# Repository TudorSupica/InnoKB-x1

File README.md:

# InnoKB-x1
 A DIY mechanical keyboard based on the ATMega32U4 MCU

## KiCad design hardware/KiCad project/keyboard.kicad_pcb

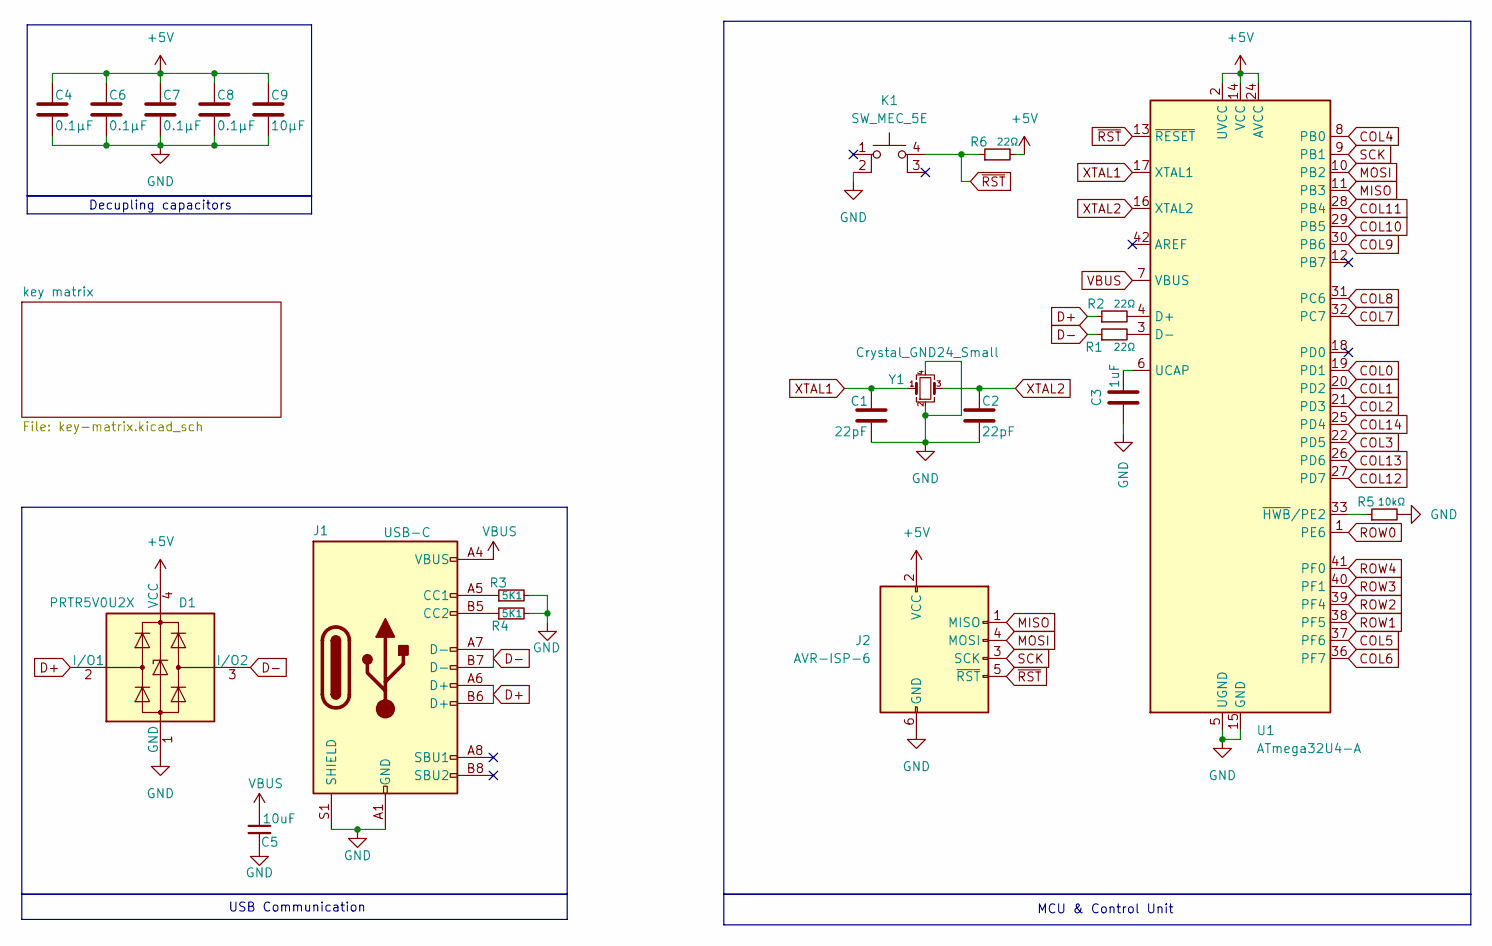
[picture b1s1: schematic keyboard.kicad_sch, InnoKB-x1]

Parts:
C1, C2: 22pF; C_0805_2012Metric_Pad1.18x1.45mm_HandSolder
C3: 1uF; C_0805_2012Metric_Pad1.18x1.45mm_HandSolder
C4, C6, C7, C8: 0.1μF; C_0805_2012Metric_Pad1.18x1.45mm_HandSolder
C5: 10uF; C_0805_2012Metric_Pad1.18x1.45mm_HandSolder
C9: 10μF; C_0805_2012Metric_Pad1.18x1.45mm_HandSolder
D1: PRTR5V0U2X; SOT-143
J1: USB-C; GSB1C41110SSHR
J2: AVR-ISP-6; PinHeader_1x06_P1.27mm_Vertical
K1: SW_MEC_5E; SW_PUSH_6mm
R1, R2, R6: 22Ω; C_0805_2012Metric_Pad1.18x1.45mm_HandSolder
R3, R4: 5K1; C_0805_2012Metric_Pad1.18x1.45mm_HandSolder
R5: 10kΩ; C_0805_2012Metric_Pad1.18x1.45mm_HandSolder
U1: ATmega32U4-A; TQFP-44_10x10mm_P0.8mm
Y1: Crystal_GND24_Small; Crystal_HC49-U-3Pin_Vertical

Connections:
+5V: C4.1, C6.1, C7.1, C8.1, C9.1, D1.4 (VCC), J2.2 (VCC), R6.2, U1.2 (UVCC), U1.14 (VCC), U1.24 (AVCC), U1.34 (VCC), U1.44 (AVCC)
COL0: U1.19 (PD1); also elsewhere on the board
COL1: U1.20 (PD2); also elsewhere on the board
COL2: U1.21 (PD3); also elsewhere on the board
COL3: U1.22 (PD5); also elsewhere on the board
COL4: U1.8 (PB0); also elsewhere on the board
COL5: U1.37 (PF6); also elsewhere on the board
COL6: U1.36 (PF7); also elsewhere on the board
COL7: U1.32 (PC7); also elsewhere on the board
COL8: U1.31 (PC6); also elsewhere on the board
COL9: U1.30 (PB6); also elsewhere on the board
COL10: U1.29 (PB5); also elsewhere on the board
COL11: U1.28 (PB4); also elsewhere on the board
COL12: U1.27 (PD7); also elsewhere on the board
COL13: U1.26 (PD6); also elsewhere on the board
COL14: U1.25 (PD4); also elsewhere on the board
D+: D1.2 (I/O1), J1.A6 (D+), J1.B6 (D+), R2.1
D-: D1.3 (I/O2), J1.A7 (D-), J1.B7 (D-), R1.1
GND: C1.2, C2.2, C3.1, C4.2, C5.2, C6.2, C7.2, C8.2, C9.2, D1.1 (GND), J1.A1 (GND), J1.A12 (GND), J1.B1 (GND), J1.B12 (GND), J1.S1 (SHIELD), J2.6 (GND), K1.2, R3.2, R4.2, R5.2, U1.5 (UGND), U1.15 (GND), U1.23 (GND), U1.35 (GND), U1.43 (GND), Y1.2, Y1.4
MISO: J2.1 (MISO), U1.11 (PB3)
MOSI: J2.4 (MOSI), U1.10 (PB2)
unnamed: J1.A5 (CC1), R3.1
unnamed: J1.B5 (CC2), R4.1
unnamed: R2.2, U1.4 (D+)
unnamed: R1.2, U1.3 (D-)
unnamed: C3.2, U1.6 (UCAP)
unnamed: R5.1, U1.33 (~HWB/PE2)
ROW0: U1.1 (PE6); also elsewhere on the board
ROW1: U1.38 (PF5); also elsewhere on the board
ROW2: U1.39 (PF4); also elsewhere on the board
ROW3: U1.40 (PF1); also elsewhere on the board
ROW4: U1.41 (PF0); also elsewhere on the board
SCK: J2.3 (SCK), U1.9 (PB1)
VBUS: C5.1, J1.A4 (VBUS), J1.A9 (VBUS), J1.B4 (VBUS), J1.B9 (VBUS), U1.7 (VBUS)
XTAL1: C1.1, U1.17 (XTAL1), Y1.1
XTAL2: C2.1, U1.16 (XTAL2), Y1.3
~RST: J2.5 (~RST), K1.4 (A), R6.1, U1.13 (~RESET)

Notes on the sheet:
USB Communication
Decupling capacitors
MCU & Control Unit

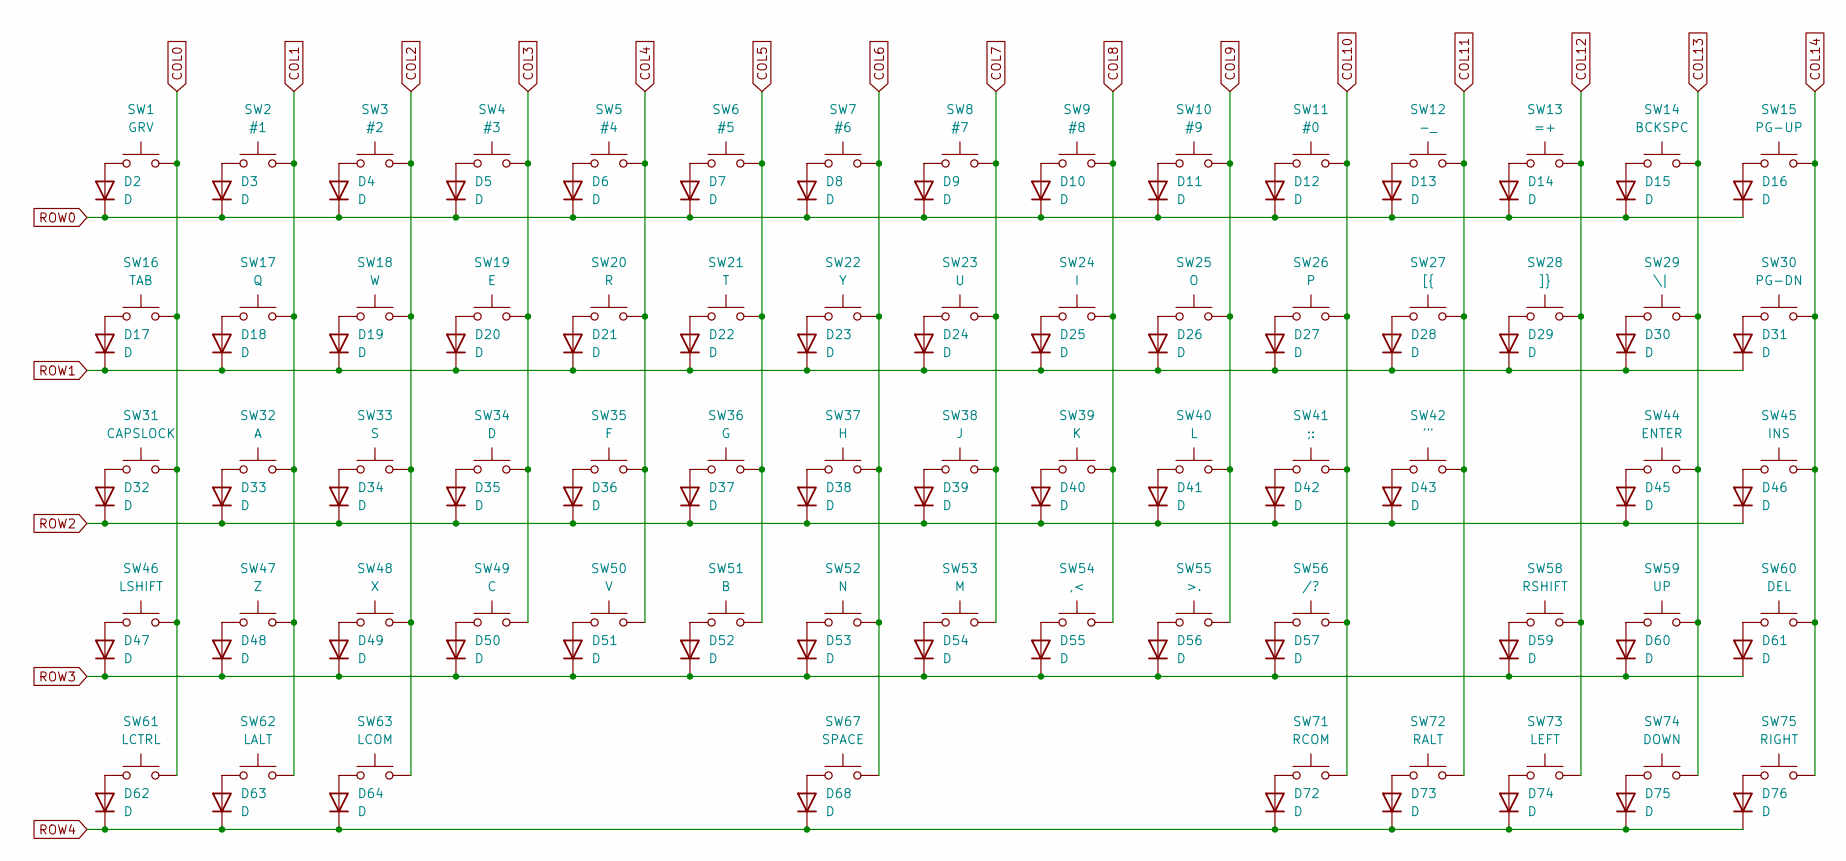
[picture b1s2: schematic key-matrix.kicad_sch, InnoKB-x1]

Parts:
D2, D3, D4, D5, D6, D7, D8, D9, D10, D11, D12, D13, D14, D15, D16, D17, D18, D19, D20, D21, D22, D23, D24, D25, D26, D27, D28, D29, D30, D31, D32, D33, D34, D35, D36, D37, D38, D39, D40, D41, D42, D43, D45, D46, D47, D48, D49, D50, D51, D52, D53, D54, D55, D56, D57, D59, D60, D61, D62, D63, D64, D68, D72, D73, D74, D75, D76: D; D_SOD-123
SW1: GRV; SW_Cherry_MX_1.00u_PCB
SW2: #1; SW_Cherry_MX_1.00u_PCB
SW3: #2; SW_Cherry_MX_1.00u_PCB
SW4: #3; SW_Cherry_MX_1.00u_PCB
SW5: #4; SW_Cherry_MX_1.00u_PCB
SW6: #5; SW_Cherry_MX_1.00u_PCB
SW7: #6; SW_Cherry_MX_1.00u_PCB
SW8: #7; SW_Cherry_MX_1.00u_PCB
SW9: #8; SW_Cherry_MX_1.00u_PCB
SW10: #9; SW_Cherry_MX_1.00u_PCB
SW11: #0; SW_Cherry_MX_1.00u_PCB
SW12: -_; SW_Cherry_MX_1.00u_PCB
SW13: =+; SW_Cherry_MX_1.00u_PCB
SW14: BCKSPC; SW_Cherry_MX_2.00u_PCB
SW15: PG-UP; SW_Cherry_MX_1.00u_PCB
SW16: TAB; SW_Cherry_MX_1.50u_PCB
SW17: Q; SW_Cherry_MX_1.00u_PCB
SW18: W; SW_Cherry_MX_1.00u_PCB
SW19: E; SW_Cherry_MX_1.00u_PCB
SW20: R; SW_Cherry_MX_1.00u_PCB
SW21: T; SW_Cherry_MX_1.00u_PCB
SW22: Y; SW_Cherry_MX_1.00u_PCB
SW23: U; SW_Cherry_MX_1.00u_PCB
SW24: I; SW_Cherry_MX_1.00u_PCB
SW25: O; SW_Cherry_MX_1.00u_PCB
SW26: P; SW_Cherry_MX_1.00u_PCB
SW27: [{; SW_Cherry_MX_1.00u_PCB
SW28: ]}; SW_Cherry_MX_1.00u_PCB
SW29: \|; SW_Cherry_MX_1.50u_PCB
SW30: PG-DN; SW_Cherry_MX_1.00u_PCB
SW31: CAPSLOCK; SW_Cherry_MX_1.75u_PCB
SW32: A; SW_Cherry_MX_1.00u_PCB
SW33: S; SW_Cherry_MX_1.00u_PCB
SW34: D; SW_Cherry_MX_1.00u_PCB
SW35: F; SW_Cherry_MX_1.00u_PCB
SW36: G; SW_Cherry_MX_1.00u_PCB
SW37: H; SW_Cherry_MX_1.00u_PCB
SW38: J; SW_Cherry_MX_1.00u_PCB
SW39: K; SW_Cherry_MX_1.00u_PCB
SW40: L; SW_Cherry_MX_1.00u_PCB
SW41: ;:; SW_Cherry_MX_1.00u_PCB
SW42: '"; SW_Cherry_MX_1.00u_PCB
SW44: ENTER; SW_Cherry_MX_2.25u_PCB
SW45: INS; SW_Cherry_MX_1.00u_PCB
SW46: LSHIFT; SW_Cherry_MX_2.25u_PCB
SW47: Z; SW_Cherry_MX_1.00u_PCB
SW48: X; SW_Cherry_MX_1.00u_PCB
SW49: C; SW_Cherry_MX_1.00u_PCB
SW50: V; SW_Cherry_MX_1.00u_PCB
SW51: B; SW_Cherry_MX_1.00u_PCB
SW52: N; SW_Cherry_MX_1.00u_PCB
SW53: M; SW_Cherry_MX_1.00u_PCB
SW54: ,<; SW_Cherry_MX_1.00u_PCB
SW55: >.; SW_Cherry_MX_1.00u_PCB
SW56: /?; SW_Cherry_MX_1.00u_PCB
SW58: RSHIFT; SW_Cherry_MX_1.75u_PCB
SW59: UP; SW_Cherry_MX_1.00u_PCB
SW60: DEL; SW_Cherry_MX_1.00u_PCB
SW61: LCTRL; SW_Cherry_MX_1.50u_PCB
SW62: LALT; SW_Cherry_MX_1.25u_PCB
SW63: LCOM; SW_Cherry_MX_1.50u_PCB
SW67: SPACE; SW_Cherry_MX_6.25u_PCB
SW71: RCOM; SW_Cherry_MX_1.00u_PCB
SW72: RALT; SW_Cherry_MX_1.25u_PCB
SW73: LEFT; SW_Cherry_MX_1.00u_PCB
SW74: DOWN; SW_Cherry_MX_1.00u_PCB
SW75: RIGHT; SW_Cherry_MX_1.00u_PCB

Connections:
COL0: SW1.2, SW16.2, SW31.2, SW46.2, SW61.2; also elsewhere on the board
COL1: SW2.2, SW17.2, SW32.2, SW47.2, SW62.2; also elsewhere on the board
COL2: SW3.2, SW18.2, SW33.2, SW48.2, SW63.2; also elsewhere on the board
COL3: SW4.2, SW19.2, SW34.2, SW49.2; also elsewhere on the board
COL4: SW5.2, SW20.2, SW35.2, SW50.2; also elsewhere on the board
COL5: SW6.2, SW21.2, SW36.2, SW51.2; also elsewhere on the board
COL6: SW7.2, SW22.2, SW37.2, SW52.2, SW67.2; also elsewhere on the board
COL7: SW8.2, SW23.2, SW38.2, SW53.2; also elsewhere on the board
COL8: SW9.2, SW24.2, SW39.2, SW54.2; also elsewhere on the board
COL9: SW10.2, SW25.2, SW40.2, SW55.2; also elsewhere on the board
COL10: SW11.2, SW26.2, SW41.2, SW56.2, SW71.2; also elsewhere on the board
COL11: SW12.2, SW27.2, SW42.2, SW72.2; also elsewhere on the board
COL12: SW13.2, SW28.2, SW58.2, SW73.2; also elsewhere on the board
COL13: SW14.2, SW29.2, SW44.2, SW59.2, SW74.2; also elsewhere on the board
COL14: SW15.2, SW30.2, SW45.2, SW60.2, SW75.2; also elsewhere on the board
unnamed: D2.2 (A), SW1.1
unnamed: D3.2 (A), SW2.1
unnamed: D4.2 (A), SW3.1
unnamed: D5.2 (A), SW4.1
unnamed: D6.2 (A), SW5.1
unnamed: D7.2 (A), SW6.1
unnamed: D8.2 (A), SW7.1
unnamed: D9.2 (A), SW8.1
unnamed: D10.2 (A), SW9.1
unnamed: D11.2 (A), SW10.1
unnamed: D12.2 (A), SW11.1
unnamed: D13.2 (A), SW12.1
unnamed: D14.2 (A), SW13.1
unnamed: D15.2 (A), SW14.1
unnamed: D16.2 (A), SW15.1
unnamed: D17.2 (A), SW16.1
unnamed: D18.2 (A), SW17.1
unnamed: D19.2 (A), SW18.1
unnamed: D20.2 (A), SW19.1
unnamed: D21.2 (A), SW20.1
unnamed: D22.2 (A), SW21.1
unnamed: D23.2 (A), SW22.1
unnamed: D24.2 (A), SW23.1
unnamed: D25.2 (A), SW24.1
unnamed: D26.2 (A), SW25.1
unnamed: D27.2 (A), SW26.1
unnamed: D28.2 (A), SW27.1
unnamed: D29.2 (A), SW28.1
unnamed: D30.2 (A), SW29.1
unnamed: D31.2 (A), SW30.1
unnamed: D32.2 (A), SW31.1
unnamed: D33.2 (A), SW32.1
unnamed: D34.2 (A), SW33.1
unnamed: D35.2 (A), SW34.1
unnamed: D36.2 (A), SW35.1
unnamed: D37.2 (A), SW36.1
unnamed: D38.2 (A), SW37.1
unnamed: D39.2 (A), SW38.1
unnamed: D40.2 (A), SW39.1
unnamed: D41.2 (A), SW40.1
unnamed: D42.2 (A), SW41.1
unnamed: D43.2 (A), SW42.1
unnamed: D45.2 (A), SW44.1
unnamed: D46.2 (A), SW45.1
unnamed: D47.2 (A), SW46.1
unnamed: D48.2 (A), SW47.1
unnamed: D49.2 (A), SW48.1
unnamed: D50.2 (A), SW49.1
unnamed: D51.2 (A), SW50.1
unnamed: D52.2 (A), SW51.1
unnamed: D53.2 (A), SW52.1
unnamed: D54.2 (A), SW53.1
unnamed: D55.2 (A), SW54.1
unnamed: D56.2 (A), SW55.1
unnamed: D57.2 (A), SW56.1
unnamed: D59.2 (A), SW58.1
unnamed: D60.2 (A), SW59.1
unnamed: D61.2 (A), SW60.1
unnamed: D62.2 (A), SW61.1
unnamed: D63.2 (A), SW62.1
unnamed: D64.2 (A), SW63.1
unnamed: D68.2 (A), SW67.1
unnamed: D72.2 (A), SW71.1
unnamed: D73.2 (A), SW72.1
unnamed: D74.2 (A), SW73.1
unnamed: D75.2 (A), SW74.1
unnamed: D76.2 (A), SW75.1
ROW0: D2.1 (K), D3.1 (K), D4.1 (K), D5.1 (K), D6.1 (K), D7.1 (K), D8.1 (K), D9.1 (K), D10.1 (K), D11.1 (K), D12.1 (K), D13.1 (K), D14.1 (K), D15.1 (K), D16.1 (K); also elsewhere on the board
ROW1: D17.1 (K), D18.1 (K), D19.1 (K), D20.1 (K), D21.1 (K), D22.1 (K), D23.1 (K), D24.1 (K), D25.1 (K), D26.1 (K), D27.1 (K), D28.1 (K), D29.1 (K), D30.1 (K), D31.1 (K); also elsewhere on the board
ROW2: D32.1 (K), D33.1 (K), D34.1 (K), D35.1 (K), D36.1 (K), D37.1 (K), D38.1 (K), D39.1 (K), D40.1 (K), D41.1 (K), D42.1 (K), D43.1 (K), D45.1 (K), D46.1 (K); also elsewhere on the board
ROW3: D47.1 (K), D48.1 (K), D49.1 (K), D50.1 (K), D51.1 (K), D52.1 (K), D53.1 (K), D54.1 (K), D55.1 (K), D56.1 (K), D57.1 (K), D59.1 (K), D60.1 (K), D61.1 (K); also elsewhere on the board
ROW4: D62.1 (K), D63.1 (K), D64.1 (K), D68.1 (K), D72.1 (K), D73.1 (K), D74.1 (K), D75.1 (K), D76.1 (K); also elsewhere on the board

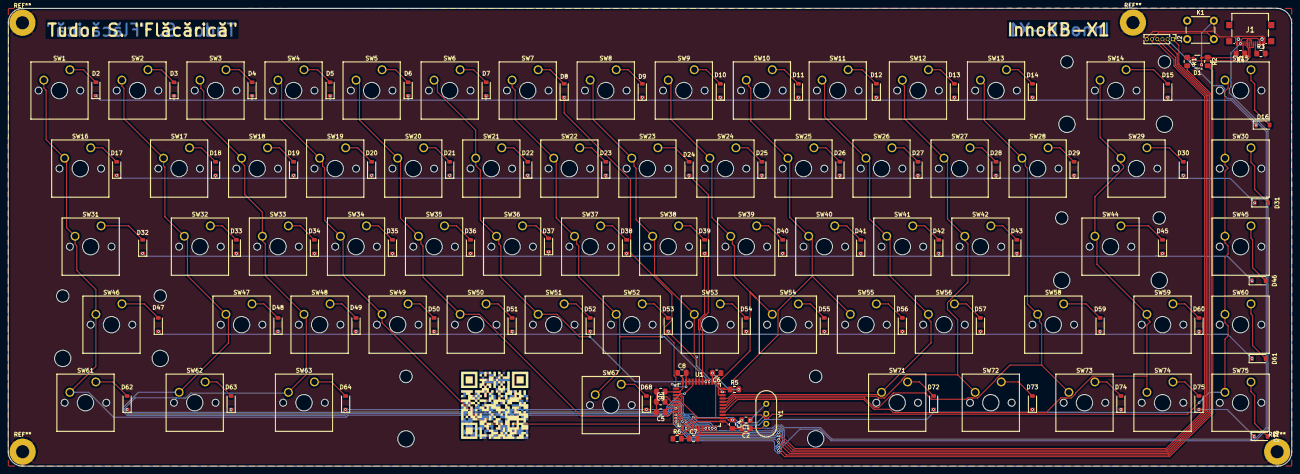
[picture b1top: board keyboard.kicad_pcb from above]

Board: 2 copper layers, 313.3 x 111.7 mm, 155 parts (0 on the bottom side), 104 nets.

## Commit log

2024-05-12 Created repository
2024-05-13 Added schematic and updated the PCB.
    Added the schematics in .jpeg form for easier access along side a new 3D render photo of the keyboard plus a new update to the PCB.
2024-07-04 Finished the PCB design
